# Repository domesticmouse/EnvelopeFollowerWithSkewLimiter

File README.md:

# ENV / SKEW — 6 HP Eurorack Envelope Follower & Asymmetric Skew Limiter

An open-source **6 HP × 3U Eurorack** audio-driven **Envelope Follower** and normal-switched **Asymmetric Skew Limiter**, designed in Python ([`SKiDL`](envelope_follower.py) + `pcbnew` + `vectorcraft-cli`) for one-cart **JLCPCB PCB + Economic Bottom-Side PCBA** and **Tayda Electronics** through-hole completion.

<p align="center">
  <a href="https://domesticmouse.github.io/EnvelopeFollowerWithSkewLimiter/"><strong>Open Live Documentation Site →</strong></a> ·
  <a href="https://domesticmouse.github.io/EnvelopeFollowerWithSkewLimiter/patches/">Patch Guides Workbench</a> ·
  <a href="https://domesticmouse.github.io/EnvelopeFollowerWithSkewLimiter/build/">Interactive Build Checklists (211 steps)</a> ·
  <a href="https://domesticmouse.github.io/EnvelopeFollowerWithSkewLimiter/hardware/">Hardware Showcase</a> ·
  <a href="https://domesticmouse.github.io/EnvelopeFollowerWithSkewLimiter/origin/">Origin Story</a> ·
  <a href="https://domesticmouse.github.io/EnvelopeFollowerWithSkewLimiter/downloads/">Fab Downloads</a>
</p>

| 6 HP Front Panel (Matte Black + ENIG) | Main PCB Top (`F.Cu` Controls) | Main PCB Bottom (`B.Cu` 50 SMDs) |
| :---: | :---: | :---: |
|  |  |  |

---

## Key Architecture & Hardware Highlights

- **Two modules in 6 HP (`30.0 × 128.5 mm` panel · `30.0 × 108.0 mm` PCB):** Patch audio into `IN` (`J1`) for **Envelope Follower Mode** (`×2.00` switchless preamp, zero-drop `BAT54S` full-wave rectifier, `SMOOTH` split-resistor passive T-filter), or patch CV/audio into `SLEW IN` (`J2`) to break the internal normal for **Asymmetric Skew Limiter Mode**.
- **Single-SKU silicon, zero trimmers:** Uses **`2× TL074HIDR`** (`8/8` op-amp sections utilized) and `14× 10 kΩ ±0.1%` thin-film resistors for `1.000×` rectifier symmetry and `0.00%` offset amplitude cross-talk across `±4.98 V` `OFFSET` (`RV4` center-detent).
- **Tuned for techno & ambient:** `FAST` (`470 nF`: `0.29–289 ms`) and `SLOW` (`4.87 µF`: `3.0 ms–3.00 s`) ranges, active post-offset *V*-to-*I* bi-color LED driver (`LED1`, Tayda `A-1076`: Green `+V` / Dark `0 V` / Red `−V`), and mirrored `OUT` (`J3`) + `INV OUT` (`J4`) outputs.
- **Friendly DIY/PCBA split:** `50` Bottom-side SMDs (`3` JLCPCB Extended SKUs + `14` Basic rows), `18` manual through-hole parts (`14` BOM rows in [`bom/ibom.html`](https://domesticmouse.github.io/EnvelopeFollowerWithSkewLimiter/bom/ibom.html)), and `12` optional DNP test points (`TP1`–`TP12`).
- **A3 Schematic & Inspection:** Explore the [interactive 9-block schematic viewer](https://domesticmouse.github.io/EnvelopeFollowerWithSkewLimiter/hardware/#schematic) or open [`envelope_follower.pdf`](envelope_follower.pdf) directly for printable bench reference.

---

## Live Documentation Site & Repository Layout

Visit **[domesticmouse.github.io/EnvelopeFollowerWithSkewLimiter](https://domesticmouse.github.io/EnvelopeFollowerWithSkewLimiter/)** for client-side `⌘K` search, interactive 6 HP patch presets, zoomable A3 schematic blocks, front-panel keepout layers, and offline-capable browser build checklists:

| Category | Repository Sources | Documentation Portal |
| :--- | :--- | :--- |
| **Patch Guides (01–08)** | [`patches/`](patches/) · [`patches/README.md`](patches/README.md) | [Studio Rack Workbench (`/patches/`)](https://domesticmouse.github.io/EnvelopeFollowerWithSkewLimiter/patches/) |
| **Build Checklists (211 steps)** | [`checklists/`](checklists/) · [`checklists/README.md`](checklists/README.md) | [Interactive Bench Checklists (`/build/`)](https://domesticmouse.github.io/EnvelopeFollowerWithSkewLimiter/build/) |
| **Interactive Assembly BOM** | [`bom/ibom.html`](bom/ibom.html) | [Launch Standalone iBOM (`/bom/ibom.html`)](https://domesticmouse.github.io/EnvelopeFollowerWithSkewLimiter/bom/ibom.html) |
| **Manufacturing Packs** | [`manufacturing/`](manufacturing/) · [`jlcpcb_bom.csv`](jlcpcb_bom.csv) | [Fabrication & Source Downloads (`/downloads/`)](https://domesticmouse.github.io/EnvelopeFollowerWithSkewLimiter/downloads/) |
| **Baseline & Critique Specs** | [`EnvelopeFollower.md`](EnvelopeFollower.md) · [`EnvelopeFollowerImprovements.md`](EnvelopeFollowerImprovements.md) | [Base Circuit & Review (`/specs/`)](https://domesticmouse.github.io/EnvelopeFollowerWithSkewLimiter/specs/) |
| **Production & Panel Specs** | [`DesignSpec.md`](DesignSpec.md) · [`panel_svg_spec.md`](panel_svg_spec.md) | [Final Design & Panel Specs (`/specs/design-spec/`)](https://domesticmouse.github.io/EnvelopeFollowerWithSkewLimiter/specs/design-spec/) |
| **Circuit & Schematic CAD** | [`envelope_follower.py`](envelope_follower.py) · [`generate_schematic.py`](generate_schematic.py) · [`envelope_follower.kicad_sch`](envelope_follower.kicad_sch) · [`envelope_follower.pdf`](envelope_follower.pdf) | [9-Block A3 Schematic (`/hardware/#schematic`)](https://domesticmouse.github.io/EnvelopeFollowerWithSkewLimiter/hardware/#schematic) |
| **Main PCB CAD & Renders** | [`generate_kicad_pcb.py`](generate_kicad_pcb.py) · [`silk_layout.json`](silk_layout.json) · [`envelope_follower.kicad_pcb`](envelope_follower.kicad_pcb) · [`images/`](images/) | [F.Cu / B.Cu PCB Plates (`/hardware/#pcb`)](https://domesticmouse.github.io/EnvelopeFollowerWithSkewLimiter/hardware/#pcb) |
| **Front Panel CAD & Artwork** | [`envelope_follower_panel.kicad_pcb`](envelope_follower_panel.kicad_pcb) · [`panel_art/`](panel_art/) | [4-Layer Panel Inspector (`/hardware/#panel`)](https://domesticmouse.github.io/EnvelopeFollowerWithSkewLimiter/hardware/#panel) |
| **Static Site & CI/CD** | [`site/`](site/) · [`.github/workflows/deploy-pages.yml`](.github/workflows/deploy-pages.yml) | [Origin Story & Lineage (`/origin/`)](https://domesticmouse.github.io/EnvelopeFollowerWithSkewLimiter/origin/) |
| **Agent Tooling & Docs** | [`AGENTS.md`](AGENTS.md) · [`GLOSSARY.md`](GLOSSARY.md) · [`docs/agents/`](docs/agents/) · [`.agents/skills/`](.agents/skills/) | — |

---

<details>
<summary><strong>Maintainer CLI: Regenerating Schematic, PCB, Panel, Renders, Checklists, iBOM & Docs Site</strong></summary>

### 1. SKiDL Netlist & KiCad 10 A3 Schematic
```bash
.venv/bin/python envelope_follower.py
.venv/bin/python generate_schematic.py
kicad-cli sch export pdf --output envelope_follower.pdf envelope_follower.kicad_sch
sips -s format png -Z 2400 envelope_follower.pdf --out images/schematic.png
```

### 2. Main PCB Layout, Silkscreen Sync & High-Res Renders
```bash
python3 generate_kicad_pcb.py
python3 generate_kicad_pcb.py --silk-only
python3 generate_kicad_pcb.py --sync-silk
python3 generate_kicad_pcb.py --show-silk [REF ...]
python3 generate_kicad_pcb.py --check-silk   # strict silkscreen collision/keepout/tether inspection
kicad-cli pcb render --side top --width 900 --height 2400 --background transparent --quality high --output images/pcb_front.png envelope_follower.kicad_pcb
kicad-cli pcb render --side bottom --width 900 --height 2400 --background transparent --quality high --output images/pcb_back.png envelope_follower.kicad_pcb
```

### 3. 6 HP Front Panel, ENIG/Silkscreen Import & Panel Renders
```bash
python3 .agents/skills/eurorack-panel/scripts/generate_eurorack_panel.py \
    --main-pcb envelope_follower.kicad_pcb \
    --output envelope_follower_panel.kicad_pcb \
    --blank-front \
    --title "ENVELOPE FOLLOWER + SKEW LIMITER" \
    --version "Rev 1.0" \
    --url "github.com/domesticmouse/EnvelopeFollowerWithSkewLimiter" \
    --spec-md panel_svg_spec.md \
    --drc
/Applications/KiCad/KiCad.app/Contents/Frameworks/Python.framework/Versions/Current/bin/python3 panel_art/import_svgs_to_kicad.py
kicad-cli pcb render --side top --width 900 --height 2400 --background transparent --quality high --output images/panel_front.png envelope_follower_panel.kicad_pcb
kicad-cli pcb render --side bottom --width 900 --height 2400 --background transparent --quality high --output images/panel_back.png envelope_follower_panel.kicad_pcb
```

### 4. Checklist 3D Alignment, Hand-Assembly & Bringup Screenshots
```bash
python3 checklists/generate_pcba_alignment_images.py
python3 checklists/generate_hand_assembly_images.py
python3 checklists/generate_bringup_images.py
```

### 5. Interactive Hand-Assembly BOM (`bom/ibom.html`)
To re-create [`bom/ibom.html`](bom/ibom.html) after modifying [`envelope_follower.kicad_pcb`](envelope_follower.kicad_pcb):
1. Open [`envelope_follower.kicad_pcb`](envelope_follower.kicad_pcb) in KiCad PCB Editor (`pcbnew`) and launch the [InteractiveHtmlBom](https://github.com/openscopeproject/InteractiveHtmlBom) plugin (`v2.11.1`).
2. **General** tab: keep the output directory `bom` and filename format `ibom` (writes `bom/ibom.html`).
3. **Fields** tab:
   - **Extra fields:** show `Value`, `Footprint`, `MPN`, and `Manufacturer` (omit `LCSC` and `Notes`).
   - **Board variant field:** select `JLCPCB_Class`.
   - **Variants whitelist:** select `Manual THT` only (leave `Basic`, `Extended`, `DNP THT`, and `<empty>` unselected).
4. Click **Generate BOM** and verify the output lists `14` BOM rows / `18` components (`11` Front, `7` Back).

### 6. GitHub Pages Documentation Site (`site/`)
```bash
cd site
npm ci
npm run typecheck
npm test
npm run build
npm run check
```

</details>

---

## Attribution, License & Disclaimer

- **Origin:** Built on **HAGIWO/ハギヲ** (`@solder_state`)’s open-source DIY [No. 43: $4 Envelope Follower](https://note.com/solder_state/n/n110e9ba066b3?hl=en) and the baseline circuit extraction in [domesticmouse/EnvelopeFollower](https://github.com/domesticmouse/EnvelopeFollower). Read the full engineering lineage on the [Origin Story](https://domesticmouse.github.io/EnvelopeFollowerWithSkewLimiter/origin/) page.
- **License:** Licensed under the [Apache License 2.0](LICENSE).
- **Disclaimer:** This is not an officially supported Google product.

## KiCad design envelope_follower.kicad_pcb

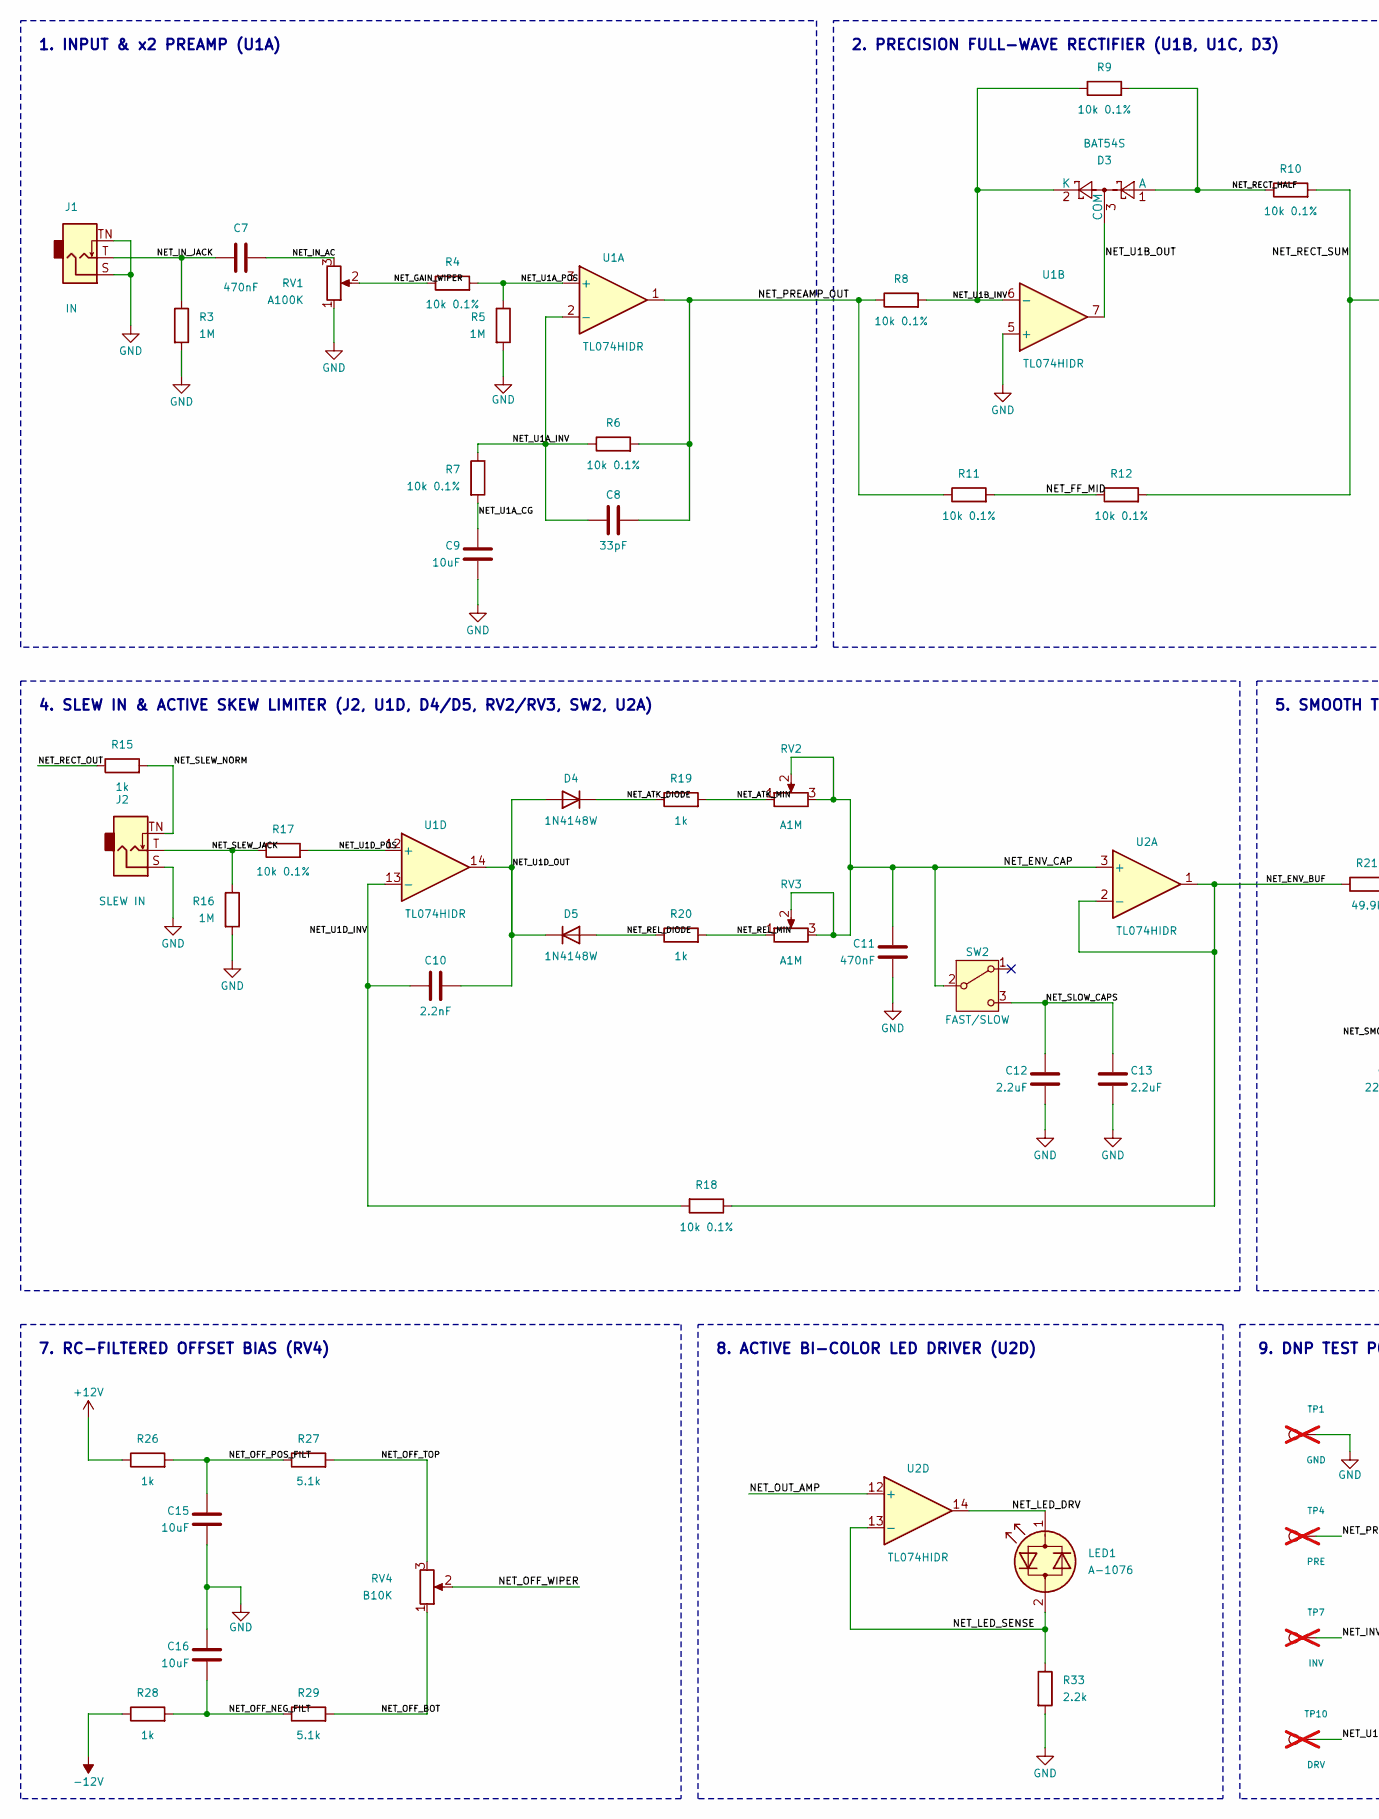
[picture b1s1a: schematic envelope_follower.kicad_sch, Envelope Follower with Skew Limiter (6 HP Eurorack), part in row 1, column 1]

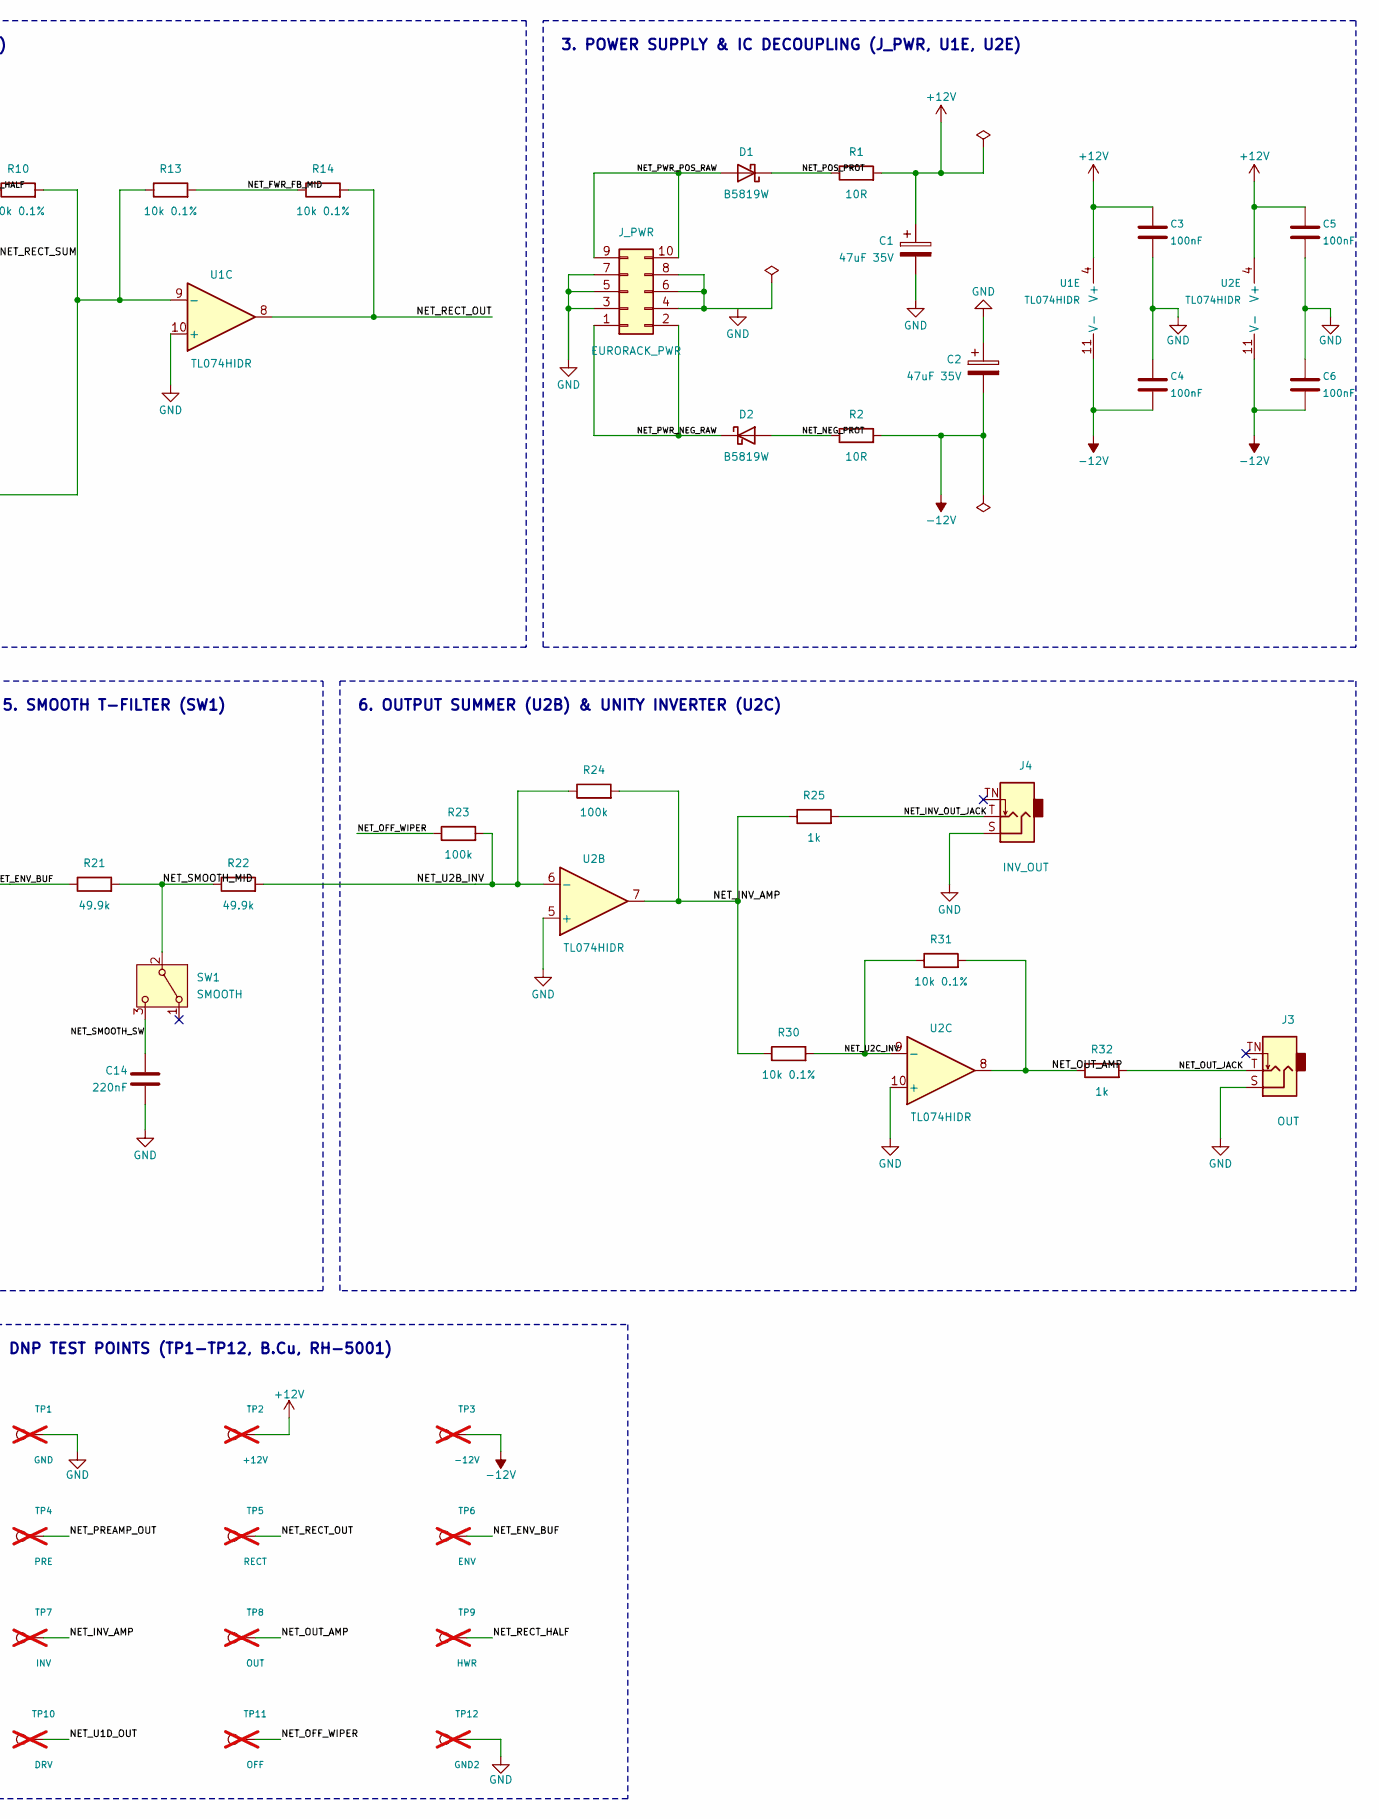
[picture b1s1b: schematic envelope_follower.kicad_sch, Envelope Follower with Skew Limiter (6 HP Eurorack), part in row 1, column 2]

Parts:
C1, C2: 47uF 35V; CP_Radial_D6.3mm_P2.50mm; MPN A-7257; JLCPCB_Class Manual THT
C3, C4, C5, C6: 100nF; C_0603_1608Metric; MPN CC0603KRX7R9BB104; LCSC C14663
C7, C11: 470nF; C_Rect_L7.2mm_W4.5mm_P5.00mm_FKS2_FKP2_MKS2_MKP2; MPN WIMA MKS2 470nF 63V; JLCPCB_Class Manual THT
C8: 33pF; C_0603_1608Metric; MPN CL10C330JB8NNNC; LCSC C1663
C9, C15, C16: 10uF; C_1206_3216Metric; MPN CL31A106KBHNNNE; LCSC C13585
C10: 2.2nF; C_0805_2012Metric; MPN CL21C222JBFNNNE; LCSC C28260
C12, C13: 2.2uF; C_Rect_L7.2mm_W7.2mm_P5.00mm_FKS2_FKP2_MKS2_MKP2; MPN WIMA MKS2 2.2uF 50V; JLCPCB_Class Manual THT
C14: 220nF; C_0805_2012Metric; MPN CL21B224KBFNNNE; LCSC C5378
D1, D2: B5819W; D_SOD-123; MPN B5819W SL; LCSC C8598
D3: BAT54S; SOT-23; MPN BAT54S; LCSC C83935
D4, D5: 1N4148W; D_SOD-123; MPN 1N4148W; LCSC C81598
J1: IN; Jack_3.5mm_QingPu_WQP-PJ398SM_Vertical_CircularHoles; MPN WQP-PJ398SM; JLCPCB_Class Manual THT
J2: SLEW IN; Jack_3.5mm_QingPu_WQP-PJ398SM_Vertical_CircularHoles; MPN WQP-PJ398SM; JLCPCB_Class Manual THT
J3: OUT; Jack_3.5mm_QingPu_WQP-PJ398SM_Vertical_CircularHoles; MPN WQP-PJ398SM; JLCPCB_Class Manual THT
J4: INV_OUT; Jack_3.5mm_QingPu_WQP-PJ398SM_Vertical_CircularHoles; MPN WQP-PJ398SM; JLCPCB_Class Manual THT
J_PWR: EURORACK_PWR; IDC-Header_2x05_P2.54mm_Vertical; MPN IDC 2x5P 2.54mm Shrouded; JLCPCB_Class Manual THT
LED1: A-1076; LED_D3.0mm; MPN A-1076; JLCPCB_Class Manual THT
R1, R2: 10R; R_0603_1608Metric; MPN 0603WAF100JT5E; LCSC C22859
R3, R5, R16: 1M; R_0603_1608Metric; MPN 0603WAF1004T5E; LCSC C22935
R4, R6, R7, R8, R9, R10, R11, R12, R13, R14, R17, R18, R30, R31: 10k 0.1%; R_0603_1608Metric; MPN RT0603BRD0710KL; LCSC C95204
R15, R19, R20, R25, R26, R28, R32: 1k; R_0603_1608Metric; MPN 0603WAF1001T5E; LCSC C21190
R21, R22: 49.9k; R_0603_1608Metric; MPN 0603WAF4992T5E; LCSC C23184
R23, R24: 100k; R_0603_1608Metric; MPN 0603WAF1003T5E; LCSC C25803
R27, R29: 5.1k; R_0603_1608Metric; MPN 0603WAF5101T5E; LCSC C23186
R33: 2.2k; R_0603_1608Metric; MPN 0603WAF2201T5E; LCSC C4190
RV1: A100K; Potentiometer_Alpha_RD901F-40-00D_Single_Vertical; MPN RD901F-40-15R1-A100K; JLCPCB_Class Manual THT
RV2, RV3: A1M; Potentiometer_Alpha_RD901F-40-00D_Single_Vertical; MPN RD901F-40-15R1-A1M; JLCPCB_Class Manual THT
RV4: B10K; Potentiometer_Alpha_RD901F-40-00D_Single_Vertical; MPN RD901F-40-15R1-B10K-0CD; JLCPCB_Class Manual THT
SW1: SMOOTH; SW_Toggle_SPDT_Dailywell_2MS1; MPN 2MS1T1B1M2QES; JLCPCB_Class Manual THT
SW2: FAST/SLOW; SW_Toggle_SPDT_Dailywell_2MS1; MPN 2MS1T1B1M2QES; JLCPCB_Class Manual THT
TP1: GND; TestPoint_Keystone_5000-5004_Miniature; MPN RH-5001; LCSC C5199801; not fitted
TP2: +12V; TestPoint_Keystone_5000-5004_Miniature; MPN RH-5001; LCSC C5199801; not fitted
TP3: -12V; TestPoint_Keystone_5000-5004_Miniature; MPN RH-5001; LCSC C5199801; not fitted
TP4: PRE; TestPoint_Keystone_5000-5004_Miniature; MPN RH-5001; LCSC C5199801; not fitted
TP5: RECT; TestPoint_Keystone_5000-5004_Miniature; MPN RH-5001; LCSC C5199801; not fitted
TP6: ENV; TestPoint_Keystone_5000-5004_Miniature; MPN RH-5001; LCSC C5199801; not fitted
TP7: INV; TestPoint_Keystone_5000-5004_Miniature; MPN RH-5001; LCSC C5199801; not fitted
TP8: OUT; TestPoint_Keystone_5000-5004_Miniature; MPN RH-5001; LCSC C5199801; not fitted
TP9: HWR; TestPoint_Keystone_5000-5004_Miniature; MPN RH-5001; LCSC C5199801; not fitted
TP10: DRV; TestPoint_Keystone_5000-5004_Miniature; MPN RH-5001; LCSC C5199801; not fitted
TP11: OFF; TestPoint_Keystone_5000-5004_Miniature; MPN RH-5001; LCSC C5199801; not fitted
TP12: GND2; TestPoint_Keystone_5000-5004_Miniature; MPN RH-5001; LCSC C5199801; not fitted
U1, U2: TL074HIDR; SOIC-14_3.9x8.7mm_P1.27mm; MPN TL074HIDR; LCSC C2878713

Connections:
+12V: C1.1, C3.1, C5.1, R1.2, R26.1, TP2.1, U1.4 (V+), U2.4 (V+)
-12V: C2.2, C4.1, C6.1, R2.2, R28.1, TP3.1, U1.11 (V-), U2.11 (V-)
GND: C1.2, C2.1, C3.2, C4.2, C5.2, C6.2, C9.2, C11.2, C12.2, C13.2, C14.2, C15.2, C16.2, J1.S, J1.TN, J2.S, J3.S, J4.S, J_PWR.3, J_PWR.4, J_PWR.5, J_PWR.6, J_PWR.7, J_PWR.8, R3.2, R5.2, R16.2, R33.2, RV1.1, TP1.1, TP12.1, U1.5 (+), U1.10 (+), U2.5 (+), U2.10 (+)
NET_ATK_DIODE: D4.1 (K), R19.1
NET_ATK_MIN: R19.2, RV2.1
NET_ENV_BUF: R18.1, R21.1, TP6.1, U2.1, U2.2 (-)
NET_ENV_CAP: C11.1, RV2.2, RV2.3, RV3.2, RV3.3, SW2.2 (B), U2.3 (+)
NET_FF_MID: R11.2, R12.1
NET_FWR_FB_MID: R13.2, R14.1
NET_GAIN_WIPER: R4.1, RV1.2
NET_INV_AMP: R24.2, R25.1, R30.1, TP7.1, U2.7
NET_INV_OUT_JACK: J4.T, R25.2
NET_IN_AC: C7.2, RV1.3
NET_IN_JACK: C7.1, J1.T, R3.1
NET_LED_DRV: LED1.1 (KA), U2.14
NET_LED_SENSE: LED1.2 (AK), R33.1, U2.13 (-)
NET_NEG_PROT: D2.2 (A), R2.1
NET_OFF_BOT: R29.2, RV4.1
NET_OFF_NEG_FILT: C16.1, R28.2, R29.1
NET_OFF_POS_FILT: C15.1, R26.2, R27.1
NET_OFF_TOP: R27.2, RV4.3
NET_OFF_WIPER: R23.1, RV4.2, TP11.1
NET_OUT_AMP: R31.2, R32.1, TP8.1, U2.8, U2.12 (+)
NET_OUT_JACK: J3.T, R32.2
NET_POS_PROT: D1.1 (K), R1.1
NET_PREAMP_OUT: C8.2, R6.2, R8.1, R11.1, TP4.1, U1.1
NET_PWR_NEG_RAW: D2.1 (K), J_PWR.1, J_PWR.2
NET_PWR_POS_RAW: D1.2 (A), J_PWR.9, J_PWR.10
NET_RECT_HALF: D3.1 (A), R9.2, R10.1, TP9.1
NET_RECT_OUT: R14.2, R15.1, TP5.1, U1.8
NET_RECT_SUM: R10.2, R12.2, R13.1, U1.9 (-)
NET_REL_DIODE: D5.2 (A), R20.1
NET_REL_MIN: R20.2, RV3.1
NET_SLEW_JACK: J2.T, R16.1, R17.1
NET_SLEW_NORM: J2.TN, R15.2
NET_SLOW_CAPS: C12.1, C13.1, SW2.3 (C)
NET_SMOOTH_MID: R21.2, R22.1, SW1.2 (B)
NET_SMOOTH_SW: C14.1, SW1.3 (C)
NET_U1A_CG: C9.1, R7.2
NET_U1A_INV: C8.1, R6.1, R7.1, U1.2 (-)
NET_U1A_POS: R4.2, R5.1, U1.3 (+)
NET_U1B_INV: D3.2 (K), R8.2, R9.1, U1.6 (-)
NET_U1B_OUT: D3.3 (COM), U1.7
NET_U1D_INV: C10.1, R18.2, U1.13 (-)
NET_U1D_OUT: C10.2, D4.2 (A), D5.1 (K), TP10.1, U1.14
NET_U1D_POS: R17.2, U1.12 (+)
NET_U2B_INV: R22.2, R23.2, R24.1, U2.6 (-)
NET_U2C_INV: R30.2, R31.1, U2.9 (-)

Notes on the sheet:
1. INPUT & x2 PREAMP (U1A)
2. PRECISION FULL-WAVE RECTIFIER (U1B, U1C, D3)
3. POWER SUPPLY & IC DECOUPLING (J_PWR, U1E, U2E)
4. SLEW IN & ACTIVE SKEW LIMITER (J2, U1D, D4/D5, RV2/RV3, SW2, U2A)
5. SMOOTH T-FILTER (SW1)
6. OUTPUT SUMMER (U2B) & UNITY INVERTER (U2C)
7. RC-FILTERED OFFSET BIAS (RV4)
8. ACTIVE BI-COLOR LED DRIVER (U2D)
9. DNP TEST POINTS (TP1-TP12, B.Cu, RH-5001)

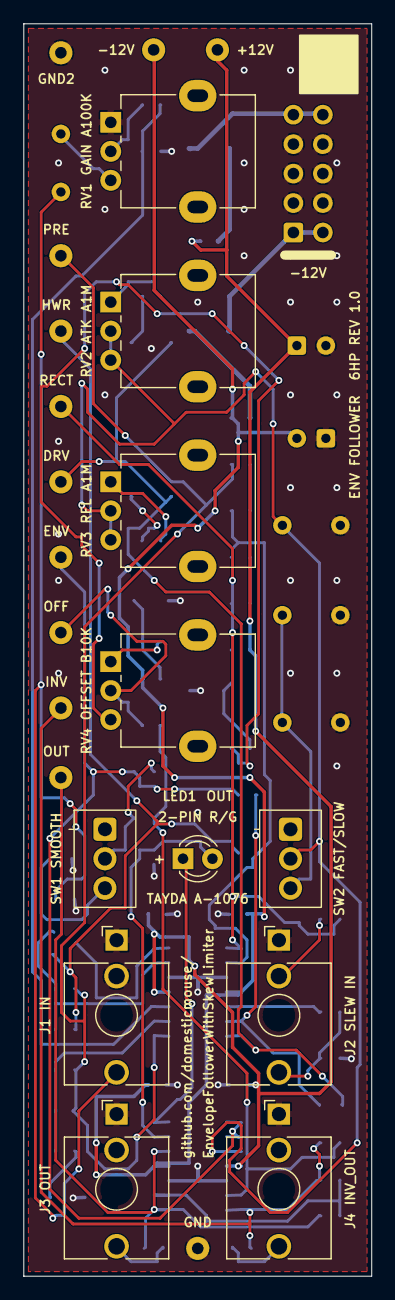
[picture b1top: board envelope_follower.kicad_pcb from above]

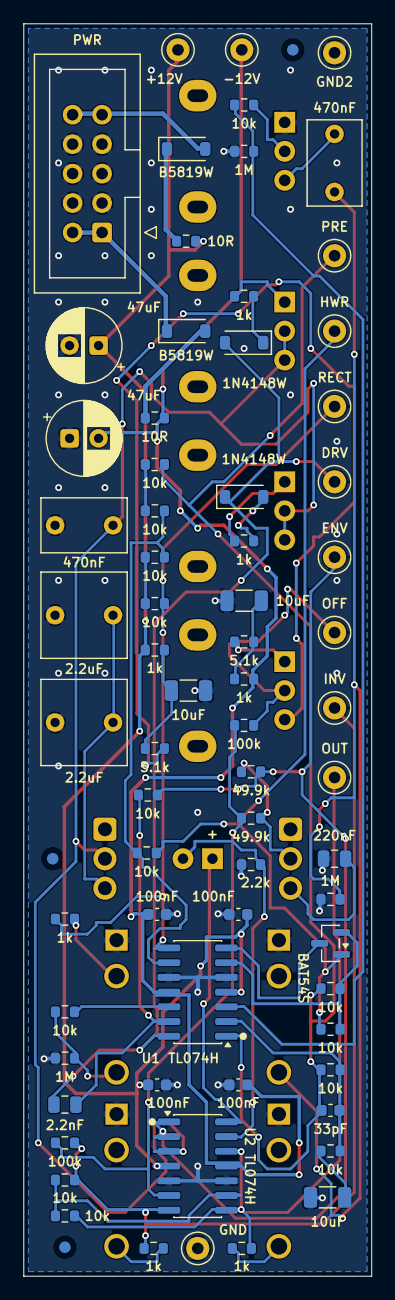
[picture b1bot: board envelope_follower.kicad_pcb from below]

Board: 2 copper layers, 30.0 x 108.0 mm, 83 parts (72 on the bottom side), 48 nets.

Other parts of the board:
FID1, FID2, FID3: Fiducial; Fiducial_1mm_Mask2mm

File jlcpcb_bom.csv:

Comment,Designator,Footprint,LCSC Part #
100nF,"C3, C4, C5, C6",C_0603_1608Metric,C14663
33pF,C8,C_0603_1608Metric,C1663
10uF,"C9, C15, C16",C_1206_3216Metric,C13585
2.2nF,C10,C_0805_2012Metric,C28260
220nF,C14,C_0805_2012Metric,C5378
B5819W,"D1, D2",D_SOD-123,C8598
BAT54S,D3,SOT-23,C83935
1N4148W,"D4, D5",D_SOD-123,C81598
10R,"R1, R2",R_0603_1608Metric,C22859
1M,"R3, R5, R16",R_0603_1608Metric,C22935
10k 0.1%,"R4, R6, R7, R8, R9, R10, R11, R12, R13, R14, R17, R18, R30, R31",R_0603_1608Metric,C95204
1k,"R15, R19, R20, R25, R26, R28, R32",R_0603_1608Metric,C21190
49.9k,"R21, R22",R_0603_1608Metric,C23184
100k,"R23, R24",R_0603_1608Metric,C25803
5.1k,"R27, R29",R_0603_1608Metric,C23186
2.2k,R33,R_0603_1608Metric,C4190
TL074HIDR,"U1, U2",SOIC-14_3.9x8.7mm_P1.27mm,C2878713
